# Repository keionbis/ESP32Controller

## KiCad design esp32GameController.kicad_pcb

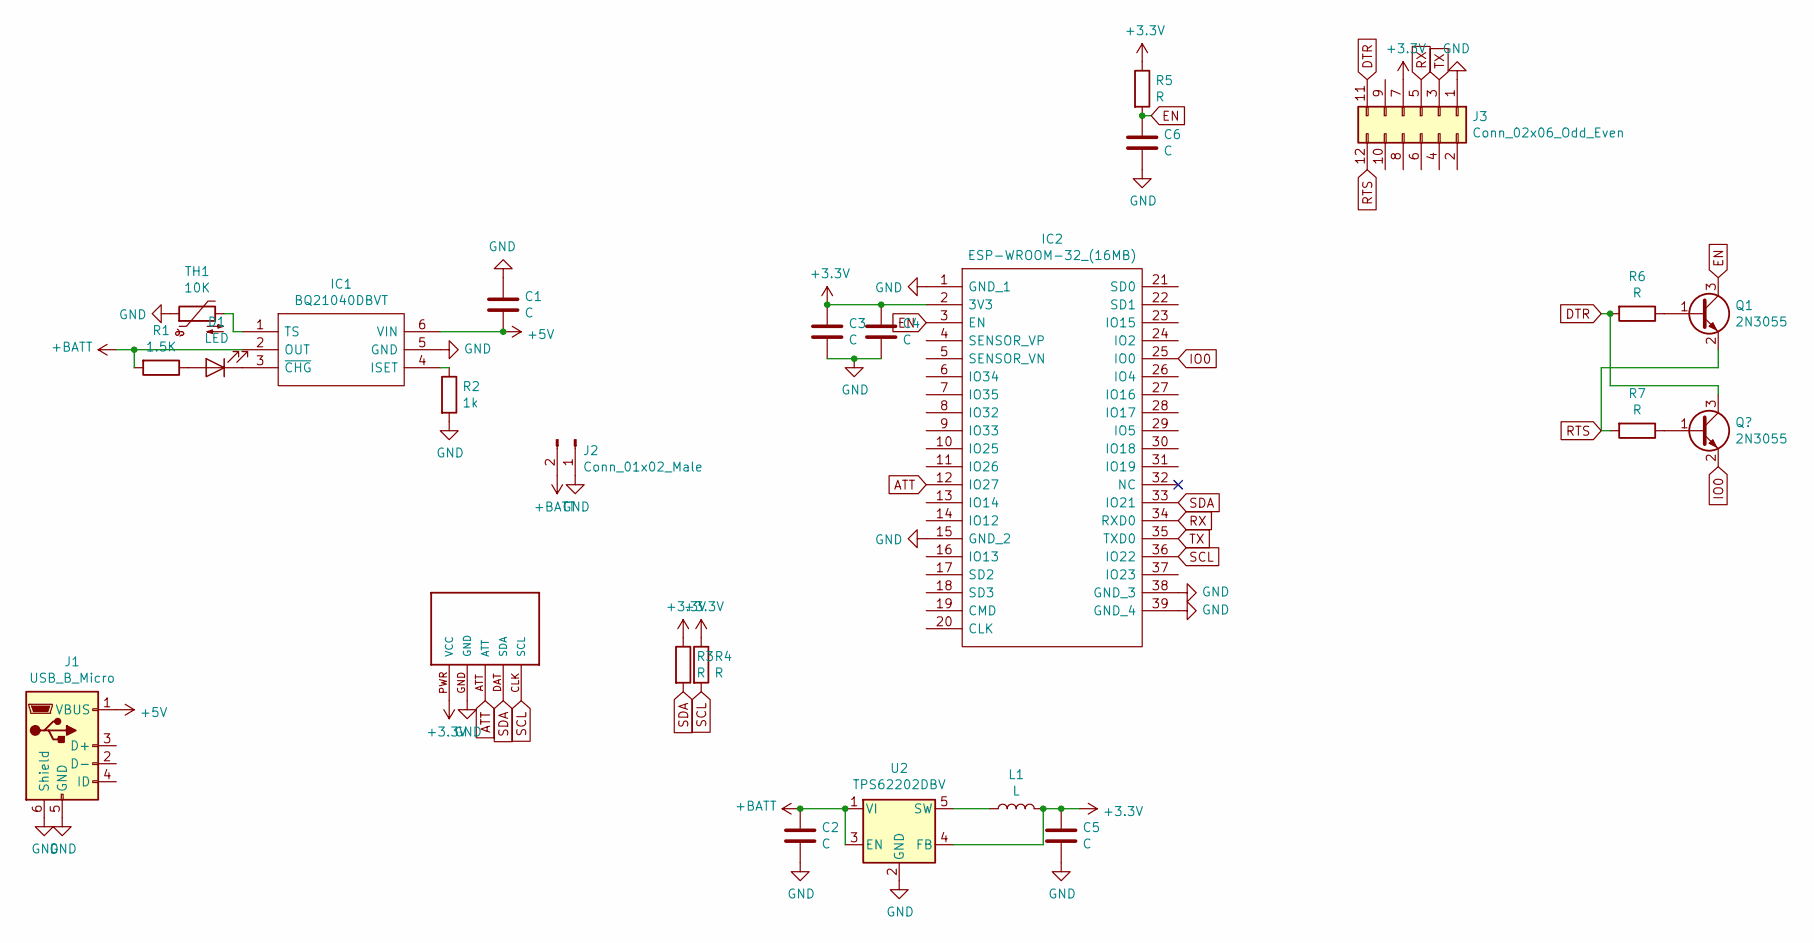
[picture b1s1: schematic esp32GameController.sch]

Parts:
C1, C2, C5: C; C_0603_1608Metric
C3, C4, C6: C; C_0402_1005Metric
D1: LED; LED_0603_1608Metric
IC1: BQ21040DBVT; SOT95P280X145-6N; Manufacturer_Part_Number BQ21040DBVT; Mouser Part Number 595-BQ21040DBVT
IC2: ESP-WROOM-32_(16MB); ESP32WROOM32D; Manufacturer_Part_Number ESP-WROOM-32 (16MB); Mouser Part Number 356-ESPWROOM3216MB
J1: USB_B_Micro; USB_Micro-B_Molex-105017-0001
J2: Conn_01x02_Male; PinHeader_1x02_P2.54mm_Vertical
J3: Conn_02x06_Odd_Even; PinHeader_2x06_P2.54mm_Vertical
L1: L; L_1210_3225Metric
Q1: 2N3055; SOT-23
R1: 1.5K; R_0402_1005Metric
R2: 1k; R_0402_1005Metric
R3, R4, R5, R6, R7: R; R_0402_1005Metric
TH1: 10K; PinHeader_1x02_P2.54mm_Vertical
U1: WIICHUCK; CHUCK
U2: TPS62202DBV; SOT-23-5

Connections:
+3V3: C3.1, C4.1, C5.1, IC2.2 (3V3), J3.7, L1.2, R3.1, R4.1, R5.1, U1.PWR (VCC), U2.4 (FB)
+5V: C1.2, IC1.6 (VIN), J1.1 (VBUS)
+BATT: C2.1, IC1.2 (OUT), J2.2, R1.2, U2.1 (VI), U2.3 (EN)
ATT: IC2.12 (IO27), U1.ATT
DTR: J3.11, R6.2; also elsewhere on the board
EN: C6.1, IC2.3 (EN), Q1.3 (C), R5.2
GND: C1.1, C2.2, C3.2, C4.2, C5.2, C6.2, IC1.5 (GND), IC2.1 (GND_1), IC2.15 (GND_2), IC2.38 (GND_3), IC2.39 (GND_4), J1.5 (GND), J1.6 (Shield), J2.1, J3.1, R2.2, TH1.1, U1.GND, U2.2 (GND)
IO0: IC2.25 (IO0); also elsewhere on the board
unnamed: D1.1 (K), IC1.3 (~CHG)
unnamed: D1.2 (A), R1.1
unnamed: IC1.1 (TS), TH1.2
unnamed: IC1.4 (ISET), R2.1
unnamed: L1.1, U2.5 (SW)
unnamed: Q1.1 (B), R6.1
unnamed 50: R7.1; also elsewhere on the board
RTS: J3.12, Q1.2 (E), R7.2
RX: IC2.34 (RXD0), J3.5
SCL: IC2.36 (IO22), R4.2, U1.CLK (SCL)
SDA: IC2.33 (IO21), R3.2, U1.DAT (SDA)
TX: IC2.35 (TXD0), J3.3

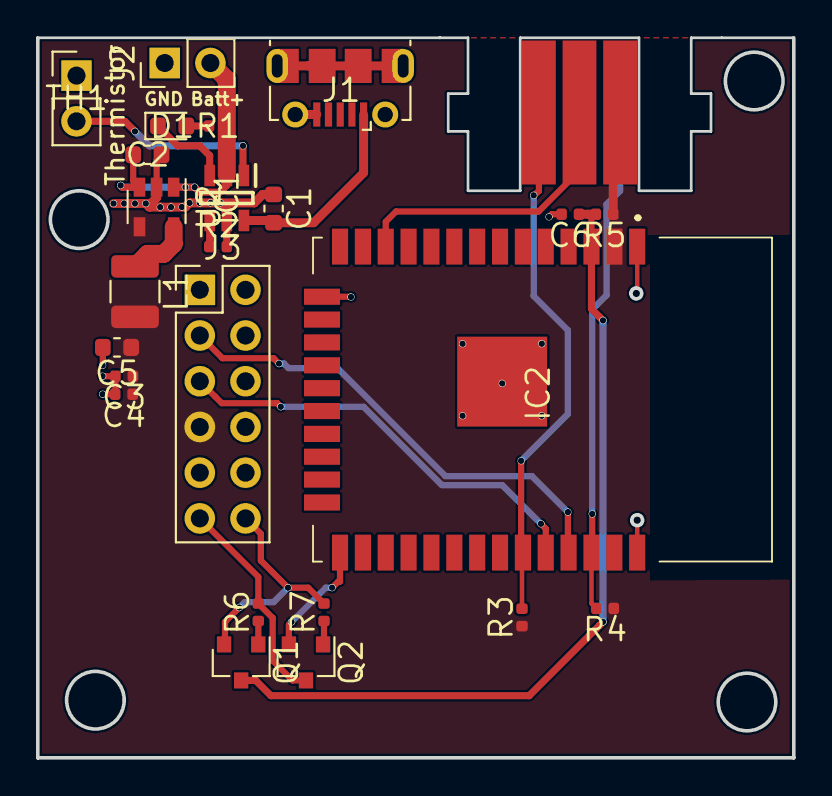
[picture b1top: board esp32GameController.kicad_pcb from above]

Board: 2 copper layers, 42.0 x 40.0 mm, 25 parts (1 on the bottom side), 20 nets.

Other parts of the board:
Q2: 2N3055; SOT-23

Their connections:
DTR: Q2.3; also elsewhere on the board
IO0: Q2.2; also elsewhere on the board
unnamed 50: Q2.1; also elsewhere on the board

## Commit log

2019-03-16 Rev1 complete
2019-03-16 Added Silk Screen
2019-03-18 Updated footprint and pinouts
2019-03-18 Updated schematic to make it easier to read
